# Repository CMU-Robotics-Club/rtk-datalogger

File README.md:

# Buggy Datalogger

[Software setup guide](https://docs.google.com/document/d/1eP9aE6b0Ft-kowX-BL1zWn5er9YviGEOUXOAjJxQ_KY/edit?tab=t.0)

Assembeled hardware:
<p align="center">

<p align="center">Image showing a module running a preliminary version of v1.0 Arduino firmware.</p>
</p>

[Project details](https://docs.google.com/document/d/1rpgdQh8PU_HBcYY4pXCmuHVJJGmpP6dXH_ktl7bgED4/edit?usp=sharing)

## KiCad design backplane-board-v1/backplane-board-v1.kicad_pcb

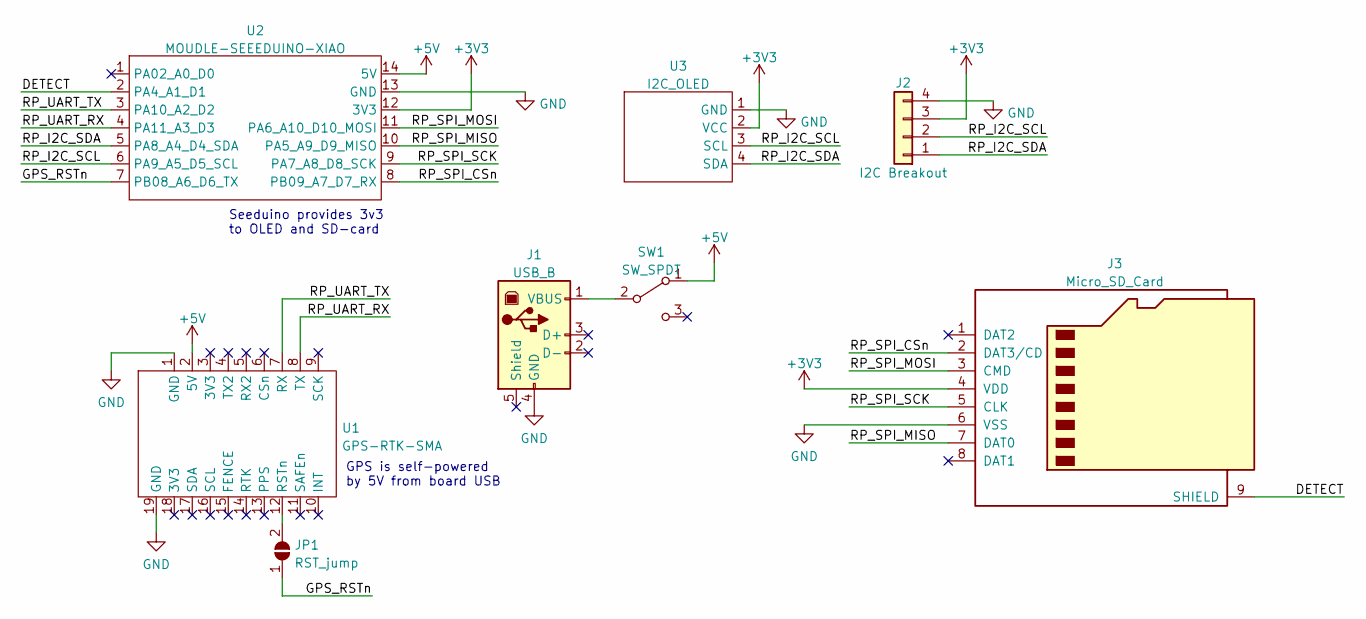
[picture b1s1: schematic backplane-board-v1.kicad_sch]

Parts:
J1: USB_B; sparkfun_usbc
J2: I2C Breakout; PinHeader_1x04_P2.54mm_Vertical
J3: Micro_SD_Card; adafruit_microsd
JP1: RST_jump; SolderJumper-2_P1.3mm_Open_Pad1.0x1.5mm
SW1: SW_SPDT; PinHeader_1x03_P2.54mm_Vertical
U1: GPS-RTK-SMA; gps-rtk-sma
U2: MOUDLE-SEEEDUINO-XIAO; MOUDLE14P-2.54-21X17.8MM
U3: I2C_OLED; i2c-oled

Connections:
+3V3: J2.3, J3.4 (VDD), U2.12 (3V3), U3.2 (VCC)
+5V: SW1.1 (A), U1.2 (5V), U2.14 (5V)
/DETECT: J3.9 (SHIELD), U2.2 (PA4_A1_D1)
/GPS_RSTn: JP1.1 (A), U2.7 (PB08_A6_D6_TX)
/RP_I2C_SCL: J2.2, U2.6 (PA9_A5_D5_SCL), U3.3 (SCL)
/RP_I2C_SDA: J2.1, U2.5 (PA8_A4_D4_SDA), U3.4 (SDA)
/RP_SPI_CSn: J3.2 (DAT3/CD), U2.8 (PB09_A7_D7_RX)
/RP_SPI_MISO: J3.7 (DAT0), U2.10 (PA5_A9_D9_MISO)
/RP_SPI_MOSI: J3.3 (CMD), U2.11 (PA6_A10_D10_MOSI)
/RP_SPI_SCK: J3.5 (CLK), U2.9 (PA7_A8_D8_SCK)
/RP_UART_RX: U1.8 (TX), U2.4 (PA11_A3_D3)
/RP_UART_TX: U1.7 (RX), U2.3 (PA10_A2_D2)
GND: J1.4 (GND), J2.4, J3.6 (VSS), U1.1 (GND), U1.19 (GND), U2.13 (GND), U3.1 (GND)
unnamed: J1.1 (VBUS), SW1.2 (B)
unnamed: JP1.2 (B), U1.12 (RSTn)

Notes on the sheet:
Seeduino provides 3v3 to OLED and SD-card
GPS is self-powered by 5V from board USB

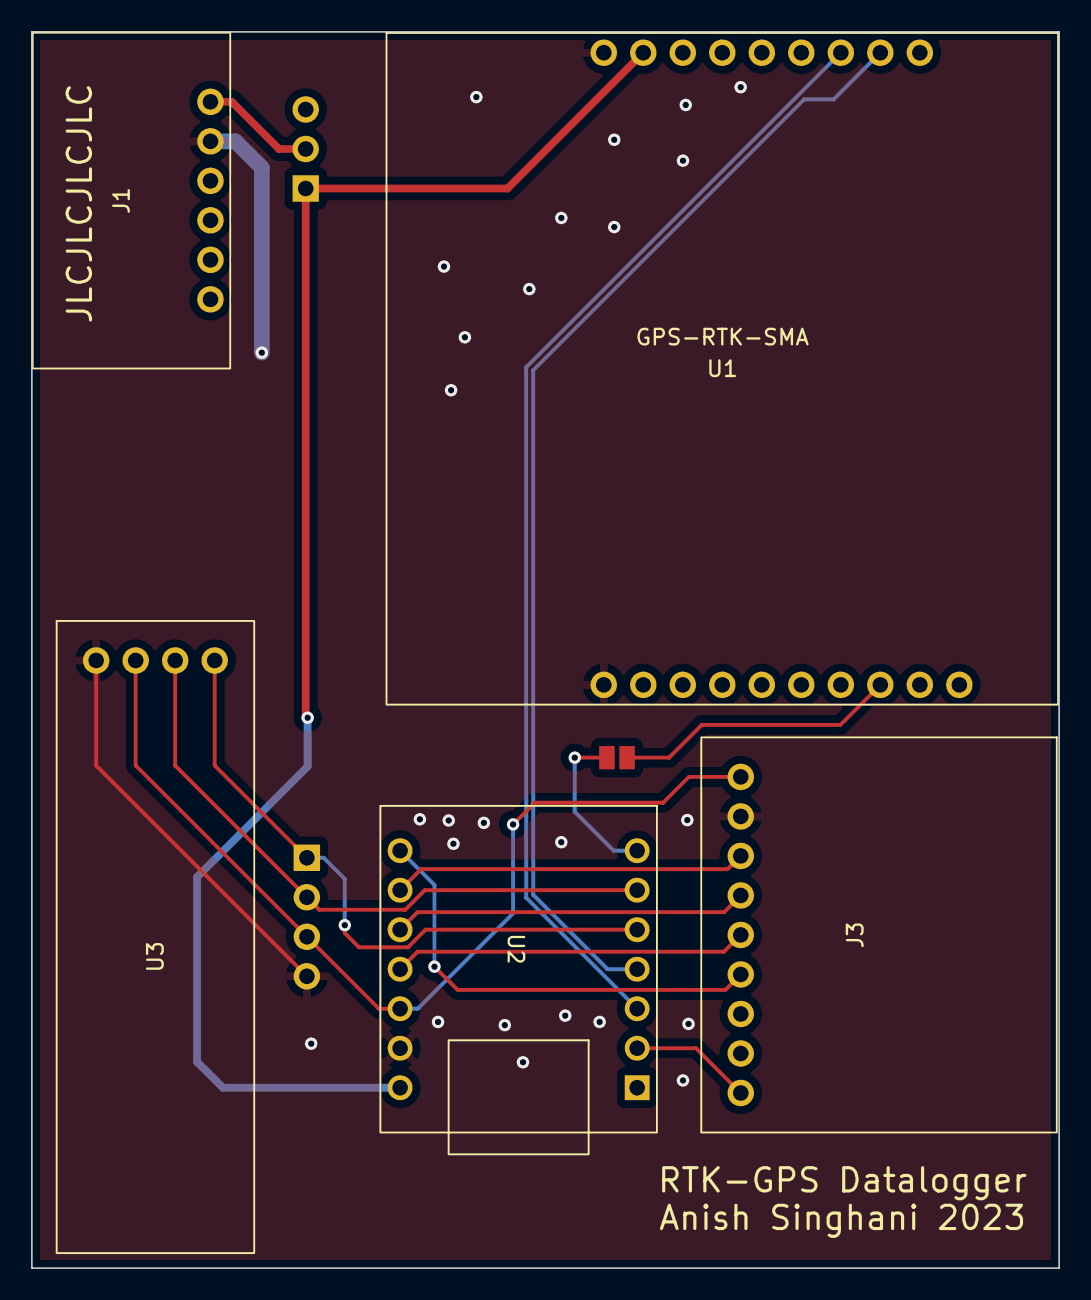
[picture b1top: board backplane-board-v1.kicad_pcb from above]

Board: 2 copper layers, 66.0 x 79.5 mm, 8 parts (0 on the bottom side), 15 nets.

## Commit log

2023-03-12 pull everything into git
2023-03-15 add scripts
2023-03-15 RTKLIB script
2023-03-24 begin work on embedded firmware
2023-06-03 update cleanup script
2023-06-04 Add backplane PCB
2023-06-07 added data directory to gitignore
2023-06-07 WIP added jupyter nb for iterative postprocessing
2023-06-07 added convbin output file size validation
2023-06-09 created function for pos to csv file
2023-06-11 updated notobook comments
2023-06-13 minor touch-ups
2023-06-13 WIP position data analysis
2023-06-13 made pipeline through the 3 notebooks smoother
    does not work with variable timestamp formats
2023-07-14 moved some notebooks into their own pipeline dir
2023-07-14 deleted empty cells in prepare-traces
    there was one empty cell that had an output image under it,
    so i didn't delete that one
2023-08-04 committing now because visualization
    in plot_trace(df) method of prepare-traces.ipynb currently works
2023-08-24 pipeline complete (visualization works)
    still have some todos
2023-09-27 started some cleanup
2023-09-28 added feature to export plot to html file
2023-10-18 Replaced python firmware with Arduino firmware v0.1
    Currently logs all data from GPS module UART1 port and displays file number and maximum buffer size (for debugging)
2023-10-19 Updated to v0.2 firmware and backed up GPS config
    Increased UART bandwidth (on GPS and microcontroller) to achieve 10Hz rates on all messages
    Also stored GPS ZED-F9P configuration to file for backup
2023-10-19 Fixed file version number
2023-10-19 Updated to v1.0 Arduino firmware
    Firmware now:
    - Prints error messages to the display
    - Uses the Seeed XIAO RP2040's onboard NeoPixel RGB LED to display status (yellow in startup, flash red in error, flash blue if no fix, flash green if fix)
    - Added error helper function to facilitate above error-displaying features
    - Catches additional error cases
    - Parses NMEA data to display the UTC time, number of satellites, and fix status to the display
2023-10-19 Added GPS config for v1.0 firmware
    Also renamed GPS config for v0.2 firmware to match
2023-10-19 Upload WorkingImage.jpg
    Added WorkingImage.jpg, which displays a module running a preliminary version of v1.0 Arduino firmware
2023-10-19 Update README.md
    Added WorkingImage.jpg and description to README.md
2023-10-25 redid velocity and acceleration calculation
2023-10-25 CLEANUP: removed all non-pipeline code
    will merge master back into this branch *somehow* before submitting a PR into master
2023-10-25 smol fix: inputPath reference in calc method
2023-10-25 added akima and cubic spline comparisson
    added data and visualizations to git tracking
2023-10-25 added lat/lon coord conversions
2023-10-25 updated postprocessing rtklib flag
2024-10-04 Full extraction notebook (course visualization currently broken)
2025-04-23 Fixed visualization link
2025-04-24 Improved instructions for mac installations
2026-02-21 Update README with link to software setup guide
